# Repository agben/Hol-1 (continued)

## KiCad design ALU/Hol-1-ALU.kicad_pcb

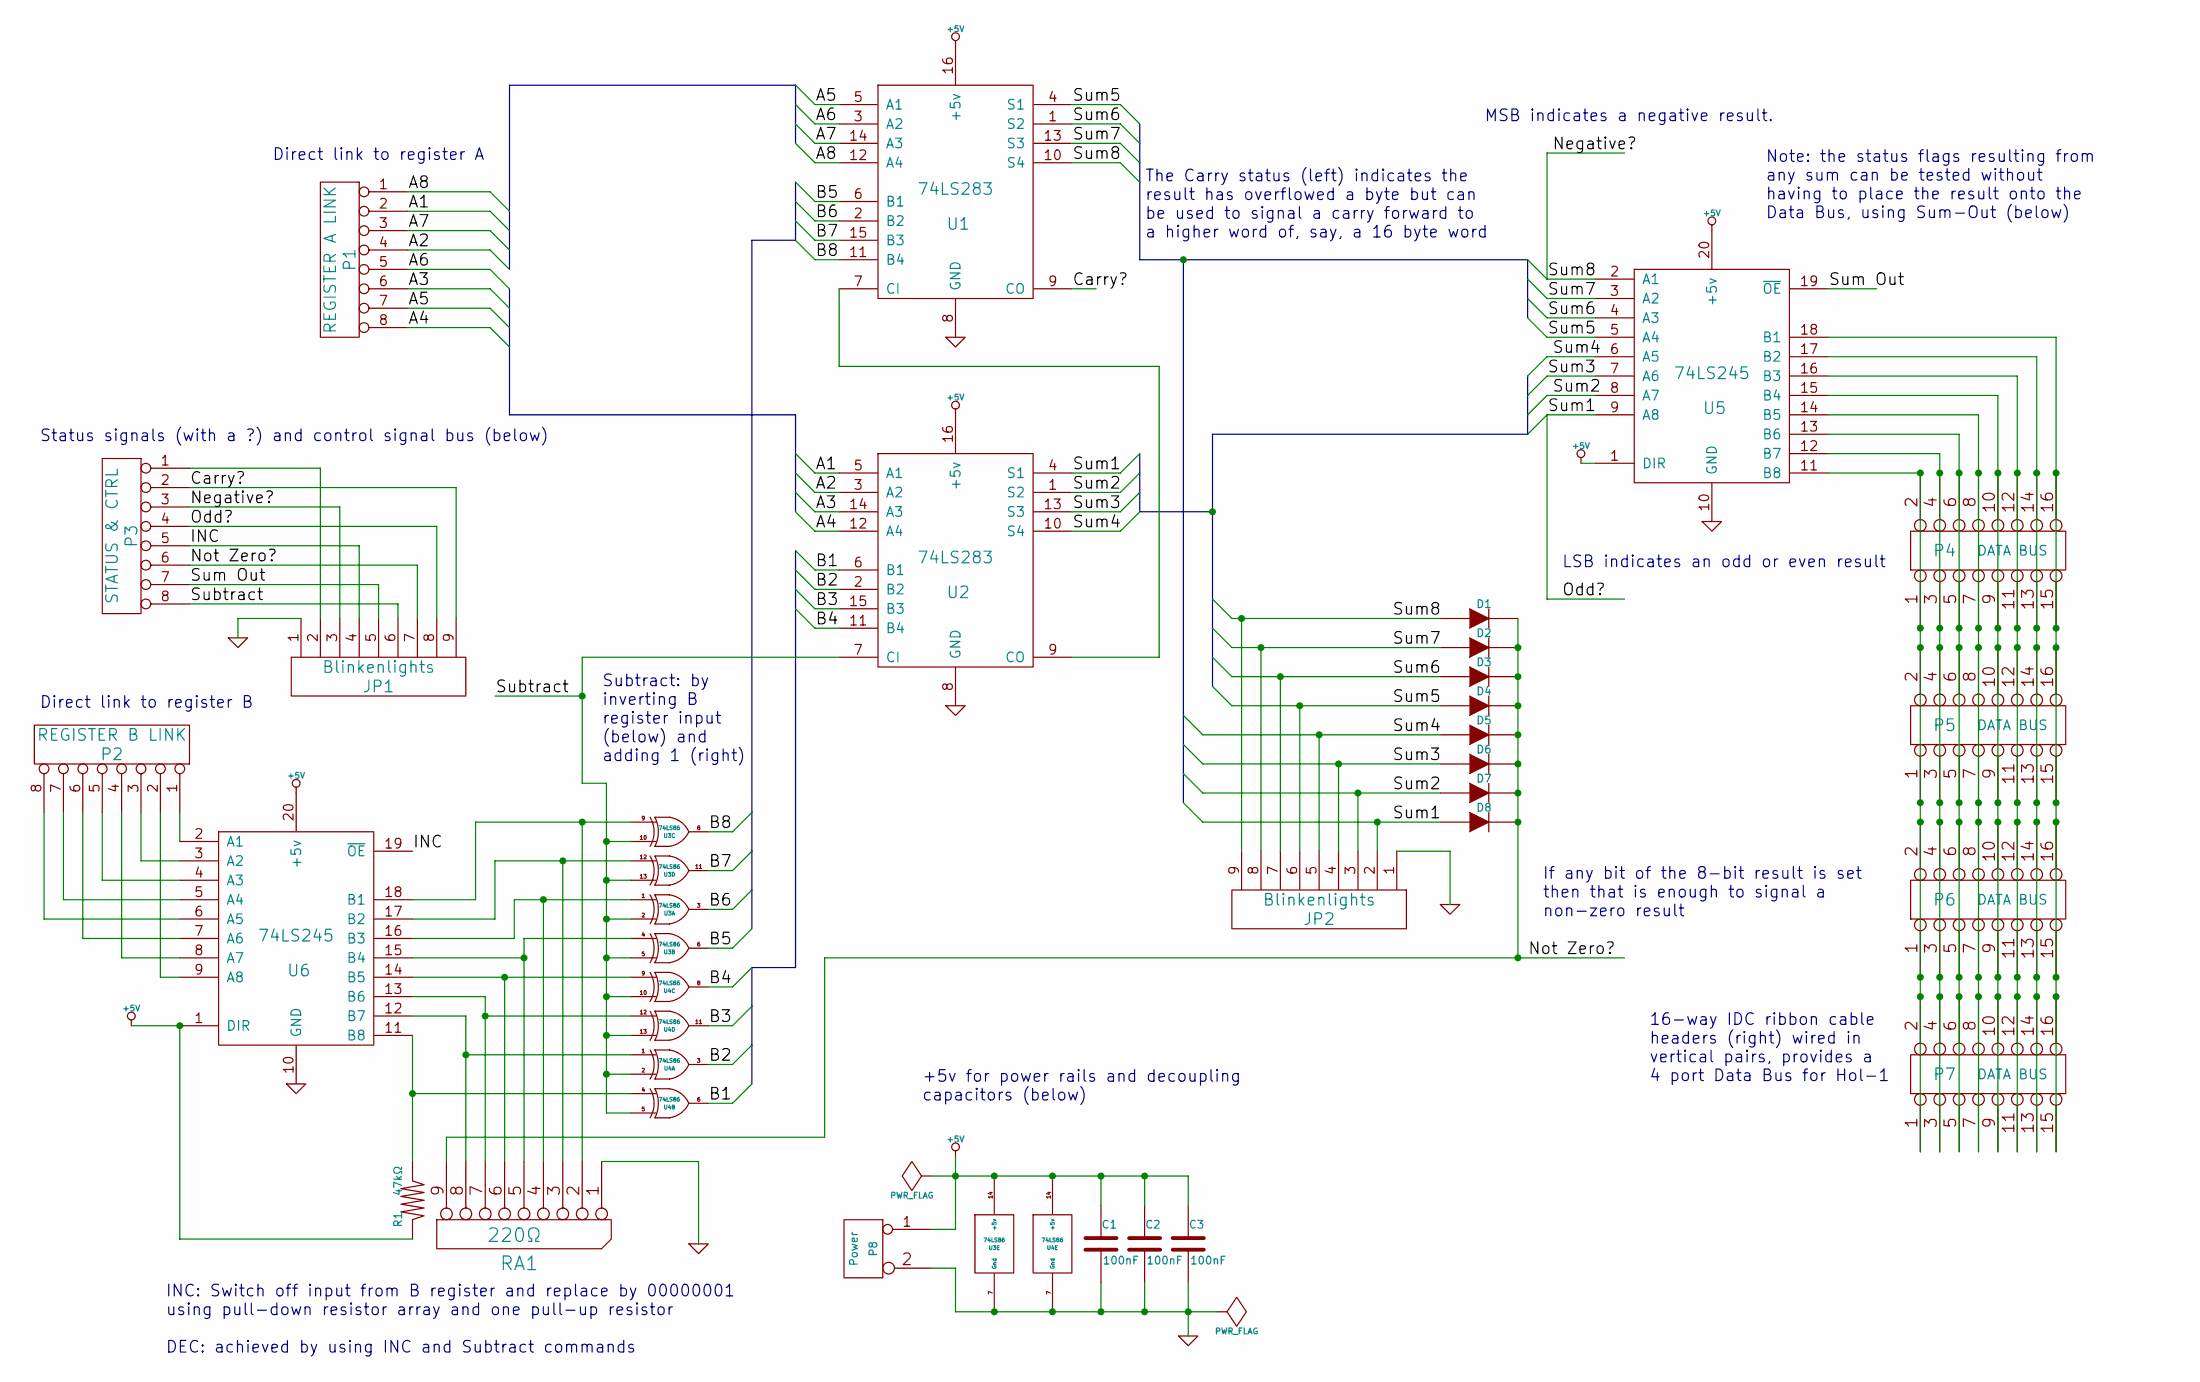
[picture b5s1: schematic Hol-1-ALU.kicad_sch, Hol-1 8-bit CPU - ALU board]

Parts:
C1, C2, C3: 100nF
D1, D2, D3, D4, D5, D6, D7, D8: DIODE
JP1, JP2: Blinkenlights
P1: REGISTER A LINK
P2: REGISTER B LINK
P3: STATUS & CTRL
P4, P5, P6, P7: DATA BUS
P8: Power
R1: 47kΩ
RA1: 220Ω
U1, U2: 74LS283
U3, U4: 74LS86
U5, U6: 74LS245

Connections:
+5V: C1.1, C2.1, C3.1, P8.1, R1.2, U1.16 (+5v), U2.16 (+5v), U3.14 (+5v), U4.14 (+5v), U5.1 (DIR), U5.20 (+5v), U6.1 (DIR), U6.20 (+5v)
/A1: P1.2, U2.5 (A1)
/A2: P1.4, U2.3 (A2)
/A3: P1.6, U2.14 (A3)
/A4: P1.8, U2.12 (A4)
/A5: P1.7, U1.5 (A1)
/A6: P1.5, U1.3 (A2)
/A7: P1.3, U1.14 (A3)
/A8: P1.1, U1.12 (A4)
/B1: U2.6 (B1), U4.6
/B2: U2.2 (B2), U4.3
/B3: U2.15 (B3), U4.11
/B4: U2.11 (B4), U4.8
/B5: U1.6 (B1), U3.6
/B6: U1.2 (B2), U3.3
/B7: U1.15 (B3), U3.11
/B8: U1.11 (B4), U3.8
/Carry?: JP1.9, P3.2, U1.9 (CO)
/INC: JP1.4, P3.5, U6.19 (~OE)
/Negative?: D1.1 (A), JP1.3, JP2.9, P3.3, U1.10 (S4), U5.2 (A1)
/Not Zero?: D1.2 (K), D2.2 (K), D3.2 (K), D4.2 (K), D5.2 (K), D6.2 (K), D7.2 (K), D8.2 (K), JP1.7, P3.6, RA1.9
/Odd?: D8.1 (A), JP1.8, JP2.2, P3.4, U2.4 (S1), U5.9 (A8)
/Subtract: JP1.6, P3.8, U2.7 (CI), U3.2, U3.5, U3.10, U3.13, U4.2, U4.5, U4.10, U4.13
/Sum2: D7.1 (A), JP2.3, U2.1 (S2), U5.8 (A7)
/Sum3: D6.1 (A), JP2.4, U2.13 (S3), U5.7 (A6)
/Sum4: D5.1 (A), JP2.5, U2.10 (S4), U5.6 (A5)
/Sum5: D4.1 (A), JP2.6, U1.4 (S1), U5.5 (A4)
/Sum6: D3.1 (A), JP2.7, U1.1 (S2), U5.4 (A3)
/Sum7: D2.1 (A), JP2.8, U1.13 (S3), U5.3 (A2)
/Sum Out: JP1.5, P3.7, U5.19 (~OE)
GND: C1.2, C2.2, C3.2, JP1.1, JP2.1, P8.2 (PM), RA1.1 (COM), U1.8 (GND), U2.8 (GND), U3.7 (Gnd), U4.7 (Gnd), U5.10 (GND), U6.10 (GND)
unnamed: U1.7 (CI), U2.9 (CO)
unnamed: RA1.5, U3.4, U6.15 (B4)
unnamed: RA1.7, U4.12, U6.13 (B6)
unnamed: RA1.8, U4.1, U6.12 (B7)
unnamed: R1.1, U4.4, U6.11 (B8)
unnamed: RA1.2, U3.9, U6.18 (B1)
unnamed: P2.1, U6.2 (A1)
unnamed: P2.7, U6.5 (A4)
unnamed: P2.2, U6.9 (A8)
unnamed: RA1.6, U4.9, U6.14 (B5)
unnamed: RA1.4, U3.1, U6.16 (B3)
unnamed: RA1.3, U3.12, U6.17 (B2)
unnamed: P2.8, U6.6 (A5)
unnamed: JP1.2, P3.1
unnamed: P2.3, U6.3 (A2)
unnamed: P2.4, U6.8 (A7)
unnamed: P2.5, U6.4 (A3)
unnamed: P2.6, U6.7 (A6)
unnamed: P4.11, P4.12, P5.11, P5.12, P6.11, P6.12, P7.11, P7.12, U5.16 (B3)
unnamed: P4.13, P4.14, P5.13, P5.14, P6.13, P6.14, P7.13, P7.14, U5.17 (B2)
unnamed: P4.15, P4.16, P5.15, P5.16, P6.15, P6.16, P7.15, P7.16, U5.18 (B1)
unnamed: P4.1, P4.2, P5.1, P5.2, P6.1, P6.2, P7.1, P7.2, U5.11 (B8)
unnamed: P4.3, P4.4, P5.3, P5.4, P6.3, P6.4, P7.3, P7.4, U5.12 (B7)
unnamed: P4.5, P4.6, P5.5, P5.6, P6.5, P6.6, P7.5, P7.6, U5.13 (B6)
unnamed: P4.7, P4.8, P5.7, P5.8, P6.7, P6.8, P7.7, P7.8, U5.14 (B5)
unnamed: P4.9, P4.10, P5.9, P5.10, P6.9, P6.10, P7.9, P7.10, U5.15 (B4)

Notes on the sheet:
INC: Switch off input from B register and replace by 00000001 using pull-down resistor array and one pull-up resistor DEC: achieved by using INC and Subtract commands
If any bit of the 8-bit result is set then that is enough to signal a non-zero result
Direct link to register B
LSB indicates an odd or even result
+5v for power rails and decoupling capacitors (below)
Note: the status flags resulting from any sum can be tested without having to place the result onto the Data Bus, using Sum-Out (below)
Status signals (with a ?) and control signal bus (below)
Direct link to register A
16-way IDC ribbon cable headers (right) wired in vertical pairs, provides a 4 port Data Bus for Hol-1
The Carry status (left) indicates the result has overflowed a byte but can be used to signal a carry forward to a higher word of, say, a 16 byte word
MSB indicates a negative result.
Subtract: by inverting B register input (below) and adding 1 (right)

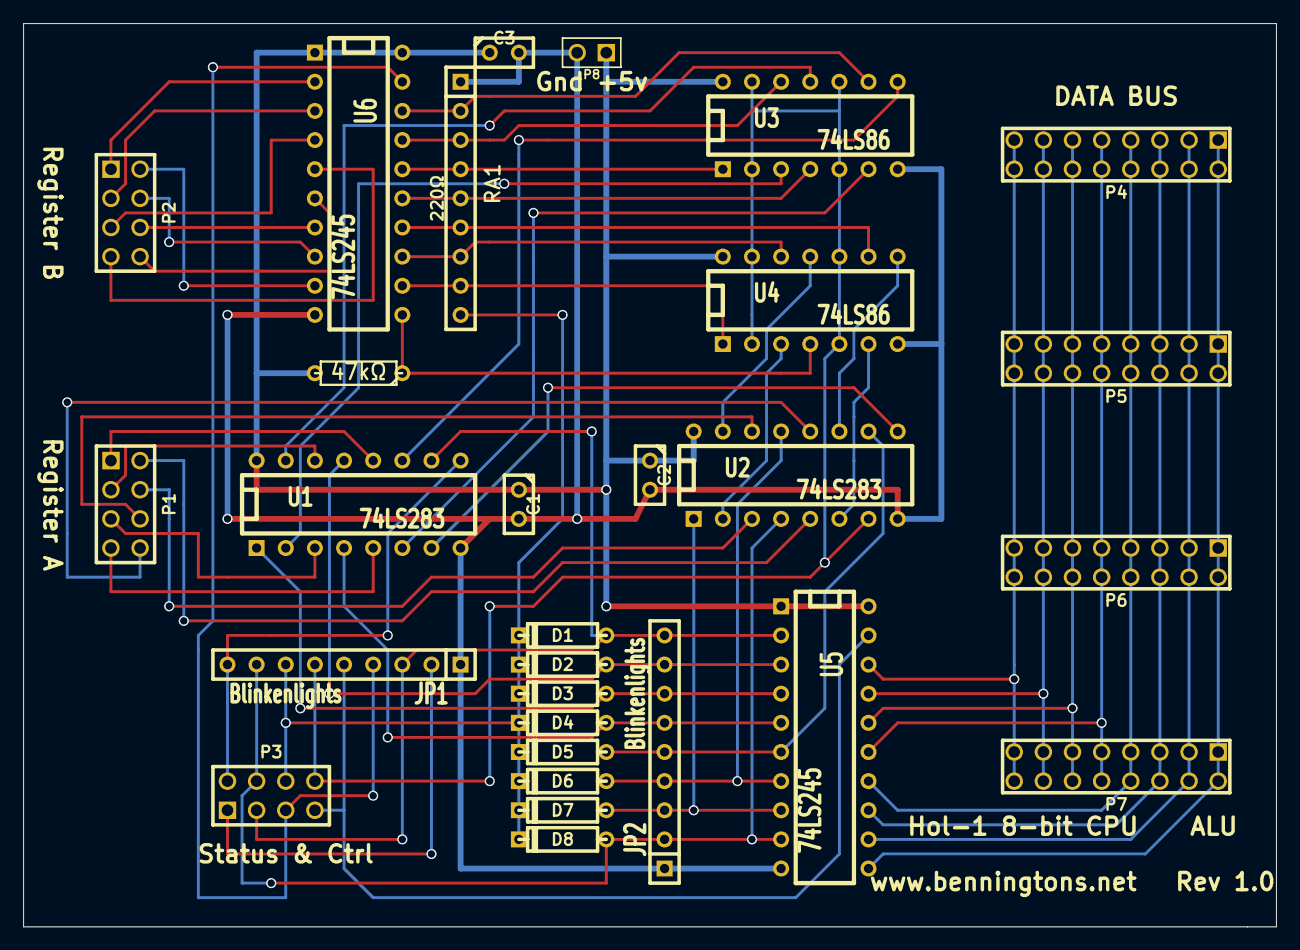
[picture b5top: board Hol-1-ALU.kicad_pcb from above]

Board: 2 copper layers, 109.2 x 78.7 mm, 29 parts (0 on the bottom side), 57 nets.

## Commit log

2019-03-04 v1.0.0 Initiate project with RAM files
2019-03-04 v1.0.1 correct links to the 'benningtons' component library
2019-03-04 v1.0.2 reduced RAM board from 31 to 30 rows to match perfboard
2019-03-07 v1.0.3 increased track width for power rails
2019-03-07 v1.0.4 rotated blinkenlight plugin to identify GND
2019-03-10 v1.1.0 draft ALU schematic added
2019-03-10 v1.1.1 inserted component library - don't hardlink outside the repo!
2019-03-10 v1.1.2 comments added to schematic
2019-03-15 v1.2.0 ALU PCB created
2019-03-15 v1.2.1 updated schematic and pcb pictures
2019-03-16 v1.2.2 resistor values added to schematic
2019-03-19 v1.3.0 schematic for registers A, B and C
2019-03-19 v1.3.1 picture of registers schematic
2019-03-21 v1.3.2 corrected register net names
2019-03-22 v1.3.3 reduce dip footprints to correct length
2019-03-23 v1.3.4 Registers PCB
2019-03-23 v1.3.5 Registers PCB image
2019-03-24 v1.3.6 silkscreen IC footprint corrections
2019-03-24 v1.3.7 make directory references relative
2019-03-30 v1.4.0 schematic for clock sources
2019-03-30 v1.4.1 pcb layout for clock sources
2019-03-30 v1.4.2 schematic correction for triggering astable clock
2019-03-31 v1.4.3 added schematic for clock selection
2019-04-06 v1.4.4 added PCB for clock selection
2019-04-23 v1.4.5 don't drive an LED directly from the clock output
2019-07-04 v1.5.0 Memory Management Unit (MMU) schematic first draft
2019-07-13 v1.5.1 MMU component footprints created
2019-07-27 v1.5.2 MMU power + blinkenlights added
2019-07-29 v1.5.3 initial MMU board layout
2019-07-29 v1.5.4 MMU add bypass caps
2019-07-30 v1.5.5 MMU reduce vias and tidy-up
2019-07-31 v1.5.6 MMU 10-pin jumpers for hex display blinkenlights
2019-08-01 v1.5.7 MMU more ergonomic layout for data input
2019-08-02 v1.5.8 MMU added blinkenlights to display memory address register
2019-08-02 v1.5.9 MMU tie unused inputs to ground
2019-08-05 v1.5.10 MMU: better space ICs
2019-08-26 v1.5.11 MMU: accommodate larger IDC headers
2019-08-26 v1.5.12 MMU: accommodate larger JST header
2019-09-08 v1.5.13 MMU: adjustments during construction
2020-01-19 v1.5.14 Registers: Re-numbered A & B ports. ALU to follow
2020-01-19 v1.5.15 ALU: Re-numbered 8 pin IDC ports to reflect the anti-clockwise numbering used
2020-01-29 v1.5.16 MMU: don't share a resistor between program and run LEDs
2020-02-03 v1.5.17 MMU: schematic and pcb layout pictures added
2020-08-15 v1.5.18 upgraded to KiCad 4.0.5
2023-06-06 v1.5.19 upgraded to KiCad 5.0
2024-05-26 v1.5.20 corrections to remove KiCad rescue libraries
2025-11-22 1.5.21 upgraded to KiCad 6.0
2025-11-23 v1.5.22 removed pre-KiCad 6.0 file types
